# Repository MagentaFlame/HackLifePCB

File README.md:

Hello!
This is a spin-off of the Starbie starter PCB project for Half Life.
I didn't have much experience, so I started off going step-by-step. However, after gaining some confidence, I made the following changes:
- changed the PCB base layer design to be the mastery symbol from League of Legends
- added sprite statuses for my poro (regular = 1 type of sprite, when sleeping, the sprite icon changes to a sleeping one, when interacting and having hearts with it, the sprite changes again)
- added a switch that would change between sprites (I'm thinking poro and soori for LOL and HLE or maybe a diff character, but yeah two different characters with unique sprites, habits, etc)

Ahead of the LOL World Championships, I hope I can create some fun things that will embody my excitement! After assembling the parts, I'll check out how the sparkle trails look - I might change them to be lines to represent rainbows or something.

Let's start with schematic.

Other than the starter project parts, I added a switch so I could change between sprites. I just connected an IO to the switch one - a simple SPST slide switch.

Next is PCB.

I made it into a mastery symbol (LOL) shape, and used the pcb routing to form the front layer's detailing while adding silkscreen on the back to make the wings and gem pop out. 

I plan to get a solder from the shop b/c I have no hardware tools basically. I have the basic arduino code modified to include sprite 1, but I plan to research a bit more during build week on how to use the switch to switch between sprites - should be just a variable connecting to the switch + a new set of variables and a few if statements, hopefully.

Here's my BOM, links can be found in my project page in Half Life and the BOM.md in github.

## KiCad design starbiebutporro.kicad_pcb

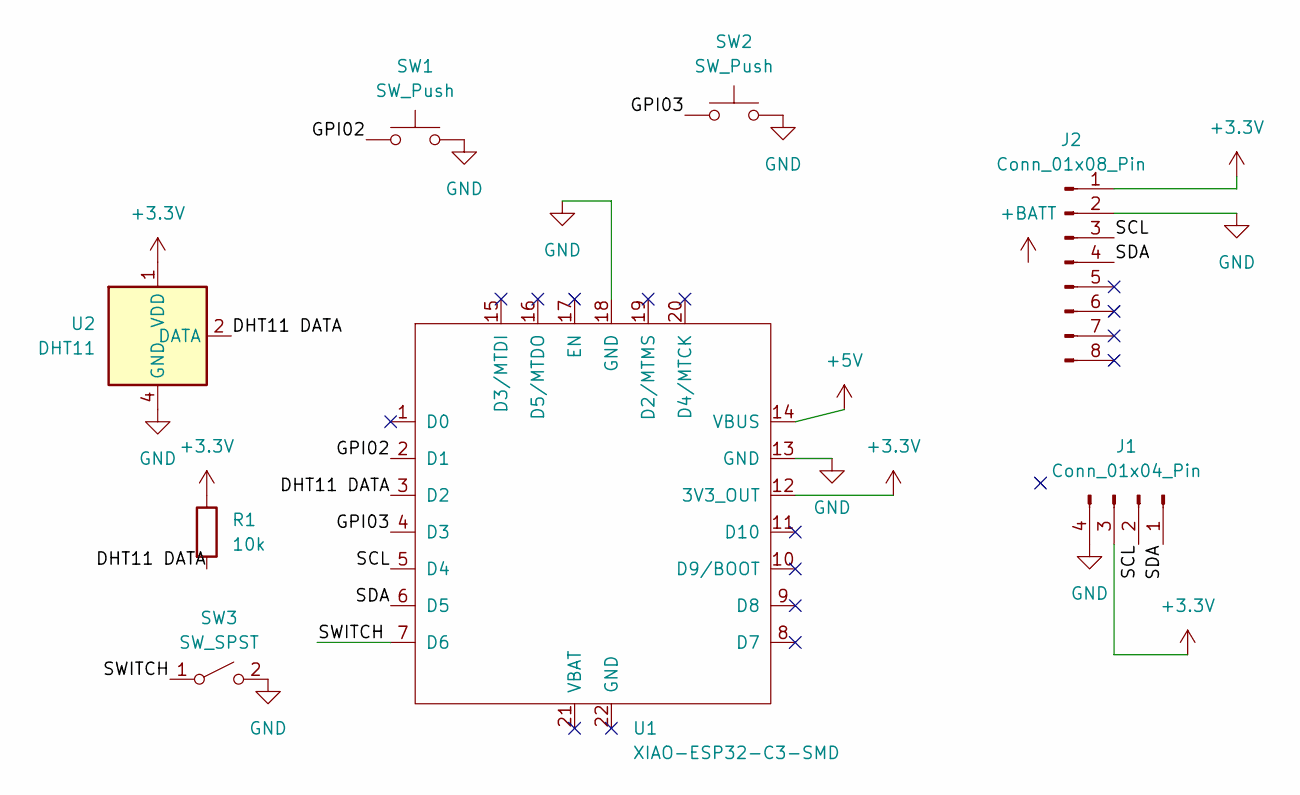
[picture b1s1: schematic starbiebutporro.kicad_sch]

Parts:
J1: Conn_01x04_Pin; Display_128x64_096_I2C
J2: Conn_01x08_Pin; PinHeader_1x08_P2.54mm_Vertical
R1: 10k; R_Axial_DIN0204_L3.6mm_D1.6mm_P7.62mm_Horizontal
SW1, SW2: SW_Push; SW_Cherry_MX_1.00u_PCB
SW3: SW_SPST; SW_DIP_SPSTx01_Slide_Copal_CHS-01A_W5.08mm_P1.27mm_JPin
U1: XIAO-ESP32-C3-SMD
U2: DHT11; Aosong_DHT11_5.5x12.0_P2.54mm

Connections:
+3.3V: J1.3, J2.1, R1.1, U1.12 (3V3_OUT), U2.1 (VDD)
+5V: U1.14 (VBUS)
/DHT11 DATA: R1.2, U1.3 (D2), U2.2 (DATA)
/GPI02: SW1.1, U1.2 (D1)
/GPI03: SW2.1, U1.4 (D3)
/SCL: J1.2, J2.3, U1.5 (D4)
/SDA: J1.1, J2.4, U1.6 (D5)
/SWITCH: SW3.1 (A), U1.7 (D6)
GND: J1.4, J2.2, SW1.2, SW2.2, SW3.2 (B), U1.13 (GND), U1.18 (GND), U2.4 (GND)

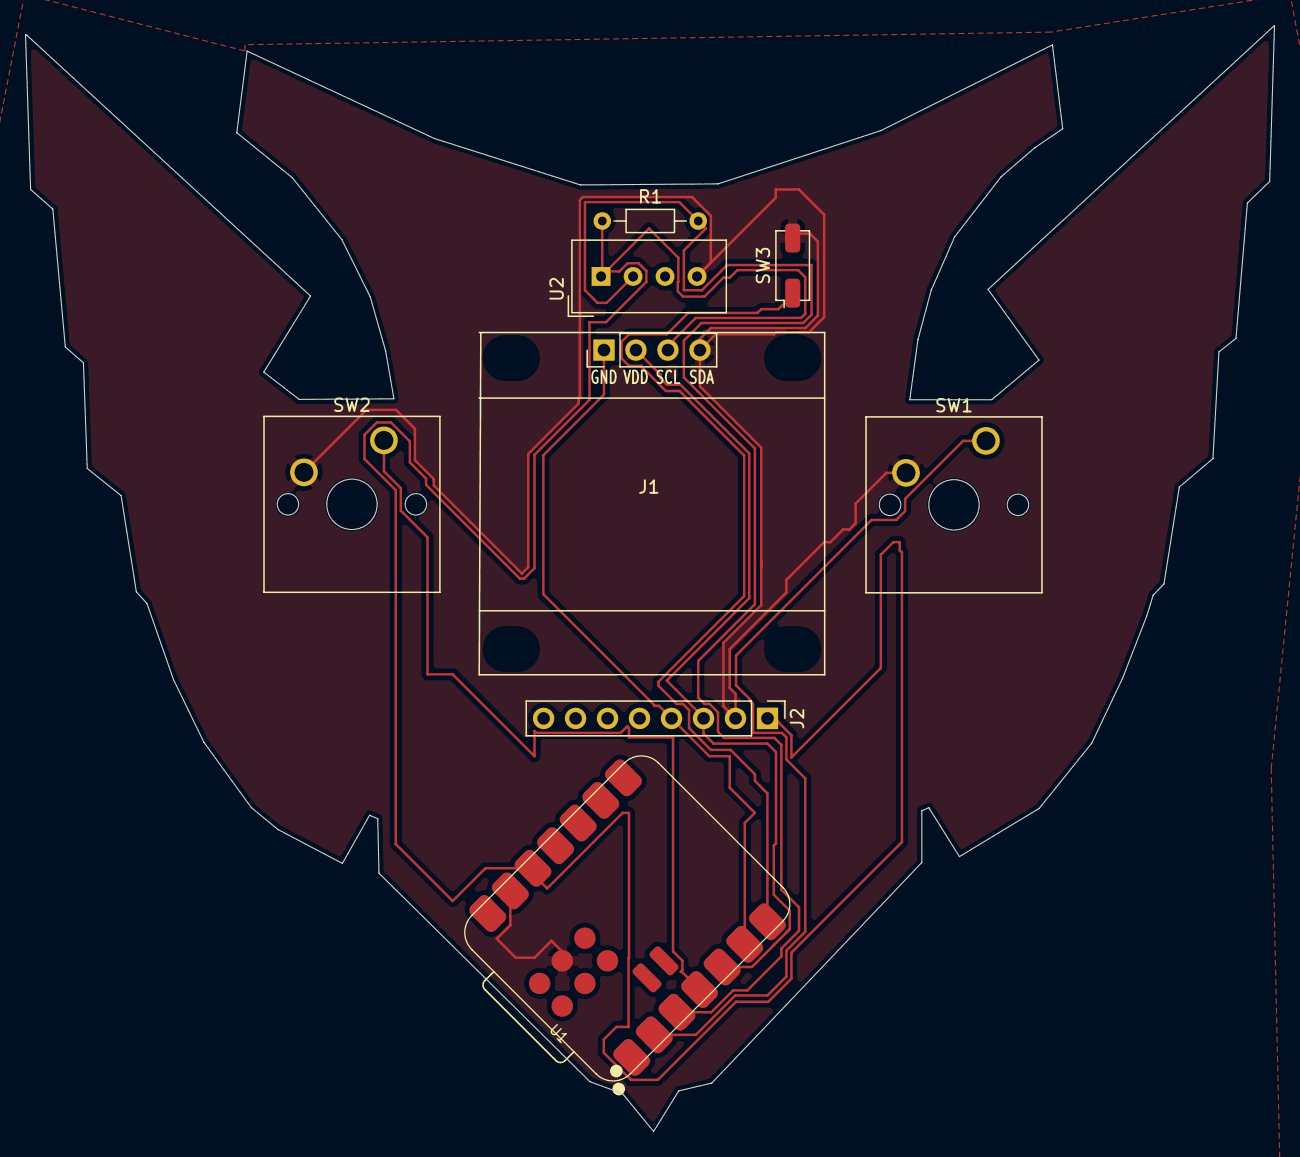
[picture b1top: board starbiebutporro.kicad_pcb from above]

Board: 2 copper layers, 99.2 x 87.8 mm, 8 parts (0 on the bottom side), 8 nets.
